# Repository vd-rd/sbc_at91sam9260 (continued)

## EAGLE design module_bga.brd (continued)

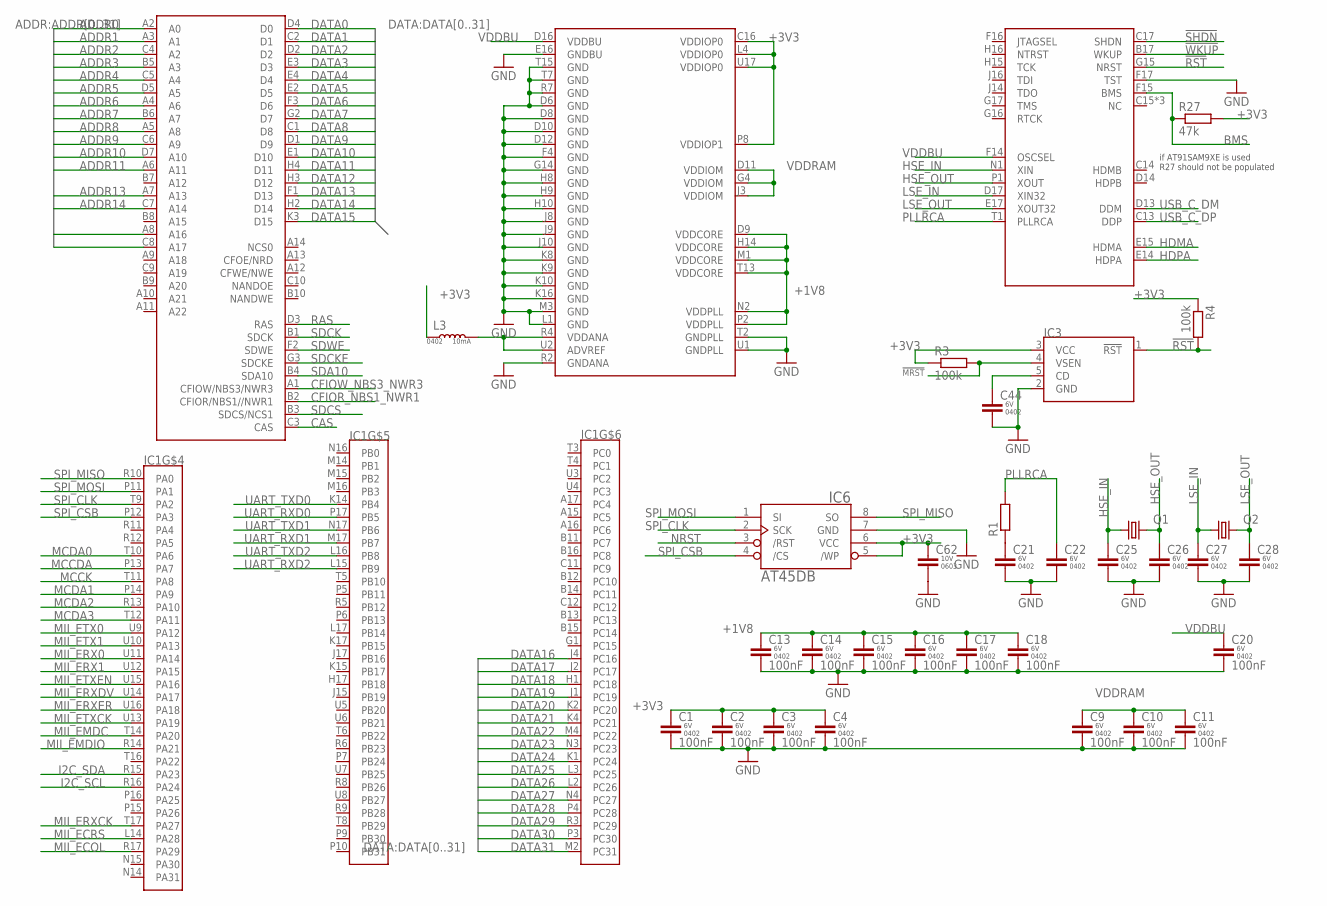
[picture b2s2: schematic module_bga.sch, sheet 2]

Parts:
C1, C2, C3, C4, C9, C10, C11, C13, C14, C15, C16, C17, C18, C20: 100nF; C0402K
C21, C22, C25, C26, C27, C28, C44: CAP-0402; C0402K
C62: CAP-0603; C0603
IC1: AT91SAM9260-BGA; BGA289C80P17X17_1500X1500X100
IC3: STM1831; SOT95P280X100-5
IC6: AT45DB-S; SOIC8_208MIL
L3: IND-0402; L0402
Q1: 3215-7; 3215
Q2: CFPX–217-NHT; 3215
R1: R-EU_R0402; R0402
R3, R4: 100k; R0402
R27: 47k; R0402

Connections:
!MRST: IC3.4 (VSEN), R3.2; also elsewhere on the board
!RST: IC1.G15 (NRST), IC3.1 (!RST), R4.2
!SHDN: IC1.C17 (SHDN)
!WKUP: IC1.B17 (WKUP); also elsewhere on the board
+1V8: C13.1, C14.1, C15.1, C16.1, C17.1, C18.1, IC1.D9 (VDDCORE), IC1.H14 (VDDCORE), IC1.M1 (VDDCORE), IC1.N2 (VDDPLL), IC1.P2 (VDDPLL), IC1.T13 (VDDCORE); also elsewhere on the board
+3V3: C1.1, C2.1, C3.1, C4.1, C62.1, IC1.C16 (VDDIOP0), IC1.L4 (VDDIOP0), IC1.P8 (VDDIOP1), IC1.U17 (VDDIOP0), IC3.3 (VCC), IC6.5 (/WP), IC6.6 (VCC), L3.1, R3.1, R4.1, R27.2; also elsewhere on the board
ADDR0: IC1.A2 (A0); also elsewhere on the board
ADDR1: IC1.A3 (A1); also elsewhere on the board
ADDR2: IC1.C4 (A2); also elsewhere on the board
ADDR3: IC1.B5 (A3); also elsewhere on the board
ADDR4: IC1.C5 (A4); also elsewhere on the board
ADDR5: IC1.D5 (A5); also elsewhere on the board
ADDR6: IC1.A4 (A6); also elsewhere on the board
ADDR7: IC1.B6 (A7); also elsewhere on the board
ADDR8: IC1.A5 (A8); also elsewhere on the board
ADDR9: IC1.C6 (A9); also elsewhere on the board
ADDR10: IC1.D7 (A10); also elsewhere on the board
ADDR11: IC1.A6 (A11); also elsewhere on the board
ADDR13: IC1.A7 (A13); also elsewhere on the board
ADDR14: IC1.C7 (A14); also elsewhere on the board
ADDR16: IC1.A8 (A16); also elsewhere on the board
ADDR17: IC1.C8 (A17); also elsewhere on the board
BMS: IC1.F15 (BMS), R27.1
CAS: IC1.C3 (CAS); also elsewhere on the board
CFIOR_NBS1_NWR1: IC1.B2 (CFIOR/NBS1//NWR1); also elsewhere on the board
CFIOW_NBS3_NWR3: IC1.A1 (CFIOW/NBS3/NWR3); also elsewhere on the board
DATA0: IC1.D4 (D0); also elsewhere on the board
DATA1: IC1.C2 (D1); also elsewhere on the board
DATA2: IC1.D2; also elsewhere on the board
DATA3: IC1.E3 (D3); also elsewhere on the board
DATA4: IC1.E4 (D4); also elsewhere on the board
DATA5: IC1.E2 (D5); also elsewhere on the board
DATA6: IC1.F3 (D6); also elsewhere on the board
DATA7: IC1.G2 (D7); also elsewhere on the board
DATA8: IC1.C1 (D8); also elsewhere on the board
DATA9: IC1.D1 (D9); also elsewhere on the board
DATA10: IC1.E1 (D10); also elsewhere on the board
DATA11: IC1.H4 (D11); also elsewhere on the board
DATA12: IC1.H3 (D12); also elsewhere on the board
DATA13: IC1.F1 (D13); also elsewhere on the board
DATA14: IC1.H2 (D14); also elsewhere on the board
DATA15: IC1.K3 (D15); also elsewhere on the board
DATA16: IC1.J4 (PC16); also elsewhere on the board
DATA17: IC1.J2 (PC17); also elsewhere on the board
DATA18: IC1.H1 (PC18); also elsewhere on the board
DATA19: IC1.J1 (PC19); also elsewhere on the board
DATA20: IC1.K2 (PC20); also elsewhere on the board
DATA21: IC1.K4 (PC21); also elsewhere on the board
DATA22: IC1.M4 (PC22); also elsewhere on the board
DATA23: IC1.N3 (PC23); also elsewhere on the board
DATA24: IC1.K1 (PC24); also elsewhere on the board
DATA25: IC1.L3 (PC25); also elsewhere on the board
DATA26: IC1.L2 (PC26); also elsewhere on the board
DATA27: IC1.N4 (PC27); also elsewhere on the board
DATA28: IC1.P4 (PC28); also elsewhere on the board
DATA29: IC1.R3 (PC29); also elsewhere on the board
DATA30: IC1.P3 (PC30); also elsewhere on the board
DATA31: IC1.M2 (PC31); also elsewhere on the board
GND: C1.2, C2.2, C3.2, C4.2, C9.2, C10.2, C11.2, C13.2, C14.2, C15.2, C16.2, C17.2, C18.2, C20.2, C21.2, C22.2, C25.2, C26.2, C27.2, C28.2, C44.2, C62.2, IC1.D6 (GND), IC1.D8 (GND), IC1.D10 (GND), IC1.D12 (GND), IC1.E16 (GNDBU), IC1.F4 (GND), IC1.F17 (TST), IC1.G14 (GND), IC1.H8 (GND), IC1.H9 (GND), IC1.H10 (GND), IC1.J8 (GND), IC1.J9 (GND), IC1.J10 (GND), IC1.K8 (GND), IC1.K9 (GND), IC1.K10 (GND), IC1.K16 (GND), IC1.L1 (GND), IC1.M3 (GND), IC1.R2 (GNDANA), IC1.R7 (GND), IC1.T2 (GNDPLL), IC1.T7 (GND), IC1.T15 (GND), IC1.U1 (GNDPLL), IC3.2 (GND), IC6.7 (GND); also elsewhere on the board
HDMA: IC1.E15 (HDMA); also elsewhere on the board
HDPA: IC1.E14 (HDPA); also elsewhere on the board
HSE_IN: C25.1, IC1.N1 (XIN), Q1.1
HSE_OUT: C26.1, IC1.P1 (XOUT), Q1.3 (2)
I2C_SCL: IC1.R16 (PA24); also elsewhere on the board
I2C_SDA: IC1.R15 (PA23); also elsewhere on the board
LSE_IN: C27.1, IC1.D17 (XIN32), Q2.1
LSE_OUT: C28.1, IC1.E17 (XOUT32), Q2.2
MCCDA: IC1.P13 (PA7); also elsewhere on the board
MCCK: IC1.T11 (PA8); also elsewhere on the board
MCDA0: IC1.T10 (PA6); also elsewhere on the board
MCDA1: IC1.P14 (PA9); also elsewhere on the board
MCDA2: IC1.R13 (PA10); also elsewhere on the board
MCDA3: IC1.T12 (PA11); also elsewhere on the board
MII_ECOL: IC1.R17 (PA29)
MII_ECRS: IC1.L14 (PA28)
MII_EMDC: IC1.T14 (PA20)
MII_EMDIO: IC1.R14 (PA21)
MII_ERX0: IC1.U11 (PA14)
MII_ERX1: IC1.U12 (PA15)
MII_ERXCK: IC1.T17 (PA27)
MII_ERXDV: IC1.U14 (PA17)
MII_ERXER: IC1.U16 (PA18)
MII_ETX0: IC1.U9 (PA12)
MII_ETX1: IC1.U10 (PA13)
MII_ETXCK: IC1.U13 (PA19)
MII_ETXEN: IC1.U15 (PA16)
unnamed: C21.1, R1.1
unnamed: C44.1, IC3.5 (CD)
unnamed: IC1.R4 (VDDANA), IC1.U2 (ADVREF), L3.2
NRST: IC6.3 (/RST); also elsewhere on the board
PLLRCA: C22.1, IC1.T1 (PLLRCA), R1.2
RAS: IC1.D3 (RAS); also elsewhere on the board
SDA10: IC1.B4 (SDA10); also elsewhere on the board
SDCK: IC1.B1 (SDCK); also elsewhere on the board
SDCKE: IC1.G3 (SDCKE); also elsewhere on the board
SDCS: IC1.B3 (SDCS/NCS1); also elsewhere on the board
SDWE: IC1.F2 (SDWE); also elsewhere on the board
SPI_CLK: IC1.T9 (PA2), IC6.2 (SCK); also elsewhere on the board
SPI_CSB: IC1.P12 (PA3), IC6.4 (/CS)
SPI_MISO: IC1.R10 (PA0), IC6.8 (SO); also elsewhere on the board
SPI_MOSI: IC1.P11 (PA1), IC6.1 (SI); also elsewhere on the board
UART_RXD0: IC1.P17 (PB5); also elsewhere on the board
UART_RXD1: IC1.M17 (PB7); also elsewhere on the board
UART_RXD2: IC1.L15 (PB9); also elsewhere on the board
UART_TXD0: IC1.K14 (PB4); also elsewhere on the board
UART_TXD1: IC1.N17 (PB6); also elsewhere on the board
UART_TXD2: IC1.L16 (PB8); also elsewhere on the board
USB_C_DM: IC1.D13 (DDM); also elsewhere on the board
USB_C_DP: IC1.C13 (DDP); also elsewhere on the board
VDDBU: C20.1, IC1.D16 (VDDBU), IC1.F14 (OSCSEL)
VDDRAM: C9.1, C10.1, C11.1, IC1.D11 (VDDIOM), IC1.G4 (VDDIOM), IC1.J3 (VDDIOM); also elsewhere on the board

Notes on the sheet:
if AT91SAM9XE is used R27 should not be populated

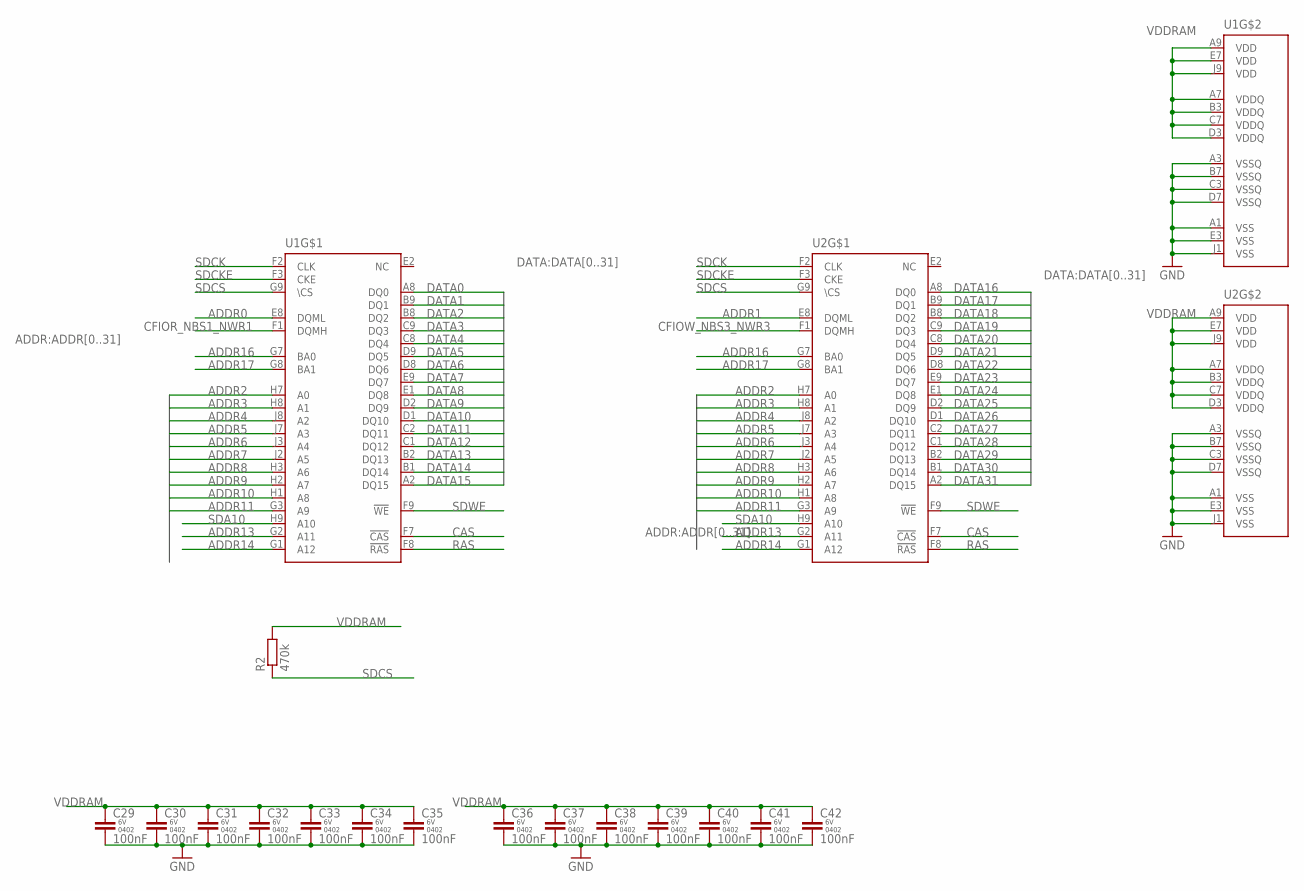
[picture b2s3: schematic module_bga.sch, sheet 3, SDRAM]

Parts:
C29, C30, C31, C32, C33, C34, C35, C36, C37, C38, C39, C40, C41, C42: 100nF; C0402K
R2: 470k; R0402
U1, U2: IS42S16160G; BGA81C80P9X9_800X800X120

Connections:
ADDR0: U1.E8 (DQML); also elsewhere on the board
ADDR1: U2.E8 (DQML); also elsewhere on the board
ADDR2: U1.H7 (A0), U2.H7 (A0); also elsewhere on the board
ADDR3: U1.H8 (A1), U2.H8 (A1); also elsewhere on the board
ADDR4: U1.J8 (A2), U2.J8 (A2); also elsewhere on the board
ADDR5: U1.J7 (A3), U2.J7 (A3); also elsewhere on the board
ADDR6: U1.J3 (A4), U2.J3 (A4); also elsewhere on the board
ADDR7: U1.J2 (A5), U2.J2 (A5); also elsewhere on the board
ADDR8: U1.H3 (A6), U2.H3 (A6); also elsewhere on the board
ADDR9: U1.H2 (A7), U2.H2 (A7); also elsewhere on the board
ADDR10: U1.H1 (A8), U2.H1 (A8); also elsewhere on the board
ADDR11: U1.G3 (A9), U2.G3 (A9); also elsewhere on the board
ADDR13: U1.G2 (A11), U2.G2 (A11); also elsewhere on the board
ADDR14: U1.G1 (A12), U2.G1 (A12); also elsewhere on the board
ADDR16: U1.G7 (BA0), U2.G7 (BA0); also elsewhere on the board
ADDR17: U1.G8 (BA1), U2.G8 (BA1); also elsewhere on the board
CAS: U1.F7 (!CAS), U2.F7 (!CAS); also elsewhere on the board
CFIOR_NBS1_NWR1: U1.F1 (DQMH); also elsewhere on the board
CFIOW_NBS3_NWR3: U2.F1 (DQMH); also elsewhere on the board
DATA0: U1.A8 (DQ0); also elsewhere on the board
DATA1: U1.B9 (DQ1); also elsewhere on the board
DATA2: U1.B8 (DQ2); also elsewhere on the board
DATA3: U1.C9 (DQ3); also elsewhere on the board
DATA4: U1.C8 (DQ4); also elsewhere on the board
DATA5: U1.D9 (DQ5); also elsewhere on the board
DATA6: U1.D8 (DQ6); also elsewhere on the board
DATA7: U1.E9 (DQ7); also elsewhere on the board
DATA8: U1.E1 (DQ8); also elsewhere on the board
DATA9: U1.D2 (DQ9); also elsewhere on the board
DATA10: U1.D1 (DQ10); also elsewhere on the board
DATA11: U1.C2 (DQ11); also elsewhere on the board
DATA12: U1.C1 (DQ12); also elsewhere on the board
DATA13: U1.B2 (DQ13); also elsewhere on the board
DATA14: U1.B1 (DQ14); also elsewhere on the board
DATA15: U1.A2 (DQ15); also elsewhere on the board
DATA16: U2.A8 (DQ0); also elsewhere on the board
DATA17: U2.B9 (DQ1); also elsewhere on the board
DATA18: U2.B8 (DQ2); also elsewhere on the board
DATA19: U2.C9 (DQ3); also elsewhere on the board
DATA20: U2.C8 (DQ4); also elsewhere on the board
DATA21: U2.D9 (DQ5); also elsewhere on the board
DATA22: U2.D8 (DQ6); also elsewhere on the board
DATA23: U2.E9 (DQ7); also elsewhere on the board
DATA24: U2.E1 (DQ8); also elsewhere on the board
DATA25: U2.D2 (DQ9); also elsewhere on the board
DATA26: U2.D1 (DQ10); also elsewhere on the board
DATA27: U2.C2 (DQ11); also elsewhere on the board
DATA28: U2.C1 (DQ12); also elsewhere on the board
DATA29: U2.B2 (DQ13); also elsewhere on the board
DATA30: U2.B1 (DQ14); also elsewhere on the board
DATA31: U2.A2 (DQ15); also elsewhere on the board
GND: C29.2, C30.2, C31.2, C32.2, C33.2, C34.2, C35.2, C36.2, C37.2, C38.2, C39.2, C40.2, C41.2, C42.2, U1.A1 (VSS), U1.A3 (VSSQ), U1.B7 (VSSQ), U1.C3 (VSSQ), U1.D7 (VSSQ), U1.E3 (VSS), U1.J1 (VSS), U2.A1 (VSS), U2.A3 (VSSQ), U2.B7 (VSSQ), U2.C3 (VSSQ), U2.D7 (VSSQ), U2.E3 (VSS), U2.J1 (VSS); also elsewhere on the board
RAS: U1.F8 (!RAS), U2.F8 (!RAS); also elsewhere on the board
SDA10: U1.H9 (A10), U2.H9 (A10); also elsewhere on the board
SDCK: U1.F2 (CLK), U2.F2 (CLK); also elsewhere on the board
SDCKE: U1.F3 (CKE), U2.F3 (CKE); also elsewhere on the board
SDCS: R2.1, U1.G9 (\CS), U2.G9 (\CS); also elsewhere on the board
SDWE: U1.F9 (!WE), U2.F9 (!WE); also elsewhere on the board
VDDRAM: C29.1, C30.1, C31.1, C32.1, C33.1, C34.1, C35.1, C36.1, C37.1, C38.1, C39.1, C40.1, C41.1, C42.1, R2.2, U1.A7 (VDDQ), U1.A9 (VDD), U1.B3 (VDDQ), U1.C7 (VDDQ), U1.D3 (VDDQ), U1.E7 (VDD), U1.J9 (VDD), U2.A7 (VDDQ), U2.A9 (VDD), U2.B3 (VDDQ), U2.C7 (VDDQ), U2.D3 (VDDQ), U2.E7 (VDD), U2.J9 (VDD); also elsewhere on the board

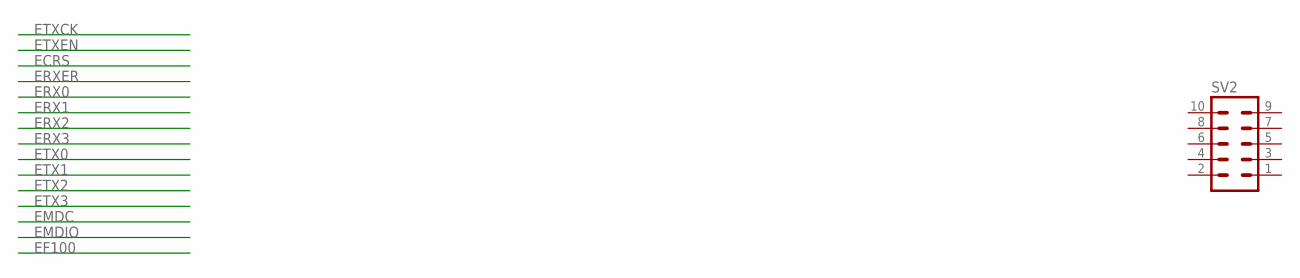
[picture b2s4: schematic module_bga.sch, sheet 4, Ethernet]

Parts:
SV2: MA05-2

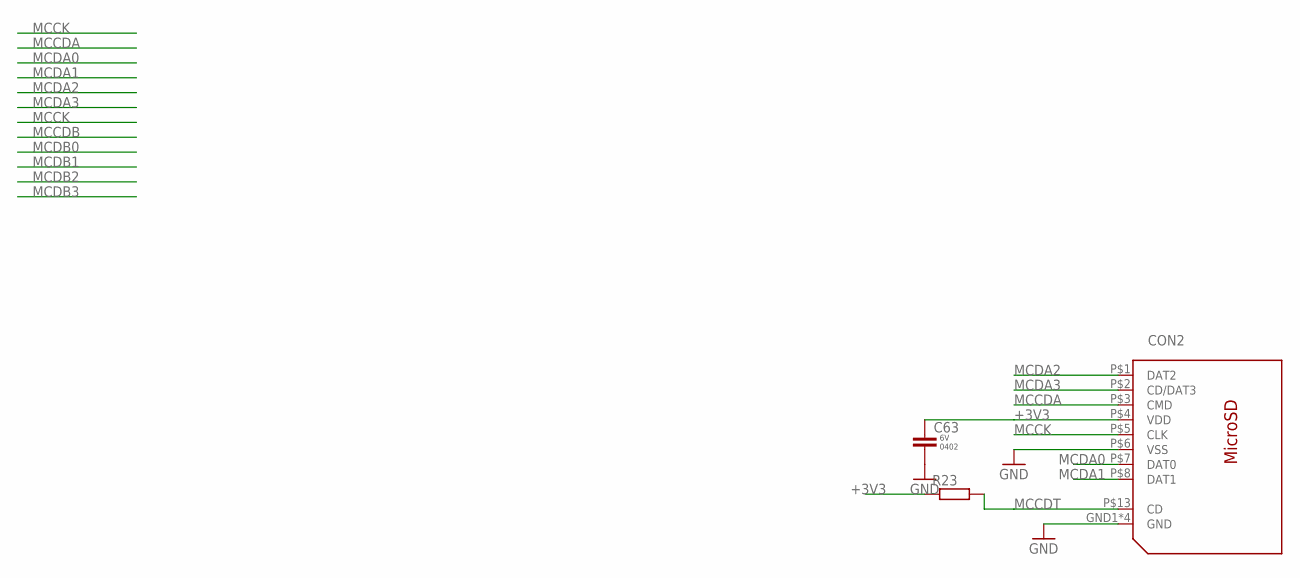
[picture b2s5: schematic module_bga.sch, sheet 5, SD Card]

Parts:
C63: CAP-0402; C0402K
CON2: 112J-TXAR; 112J
R23: R-EU_R0402; R0402

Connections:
+3V3: C63.1, CON2.P$4 (VDD), R23.1; also elsewhere on the board
GND: C63.2, CON2.GND1 (GND), CON2.GND2 (GND), CON2.GND3 (GND), CON2.GND4 (GND), CON2.P$6 (VSS); also elsewhere on the board
MCCDA: CON2.P$3 (CMD); also elsewhere on the board
MCCDT: CON2.P$13 (CD), R23.2
MCCK: CON2.P$5 (CLK); also elsewhere on the board
MCDA0: CON2.P$7 (DAT0); also elsewhere on the board
MCDA1: CON2.P$8 (DAT1); also elsewhere on the board
MCDA2: CON2.P$1 (DAT2); also elsewhere on the board
MCDA3: CON2.P$2 (CD/DAT3); also elsewhere on the board

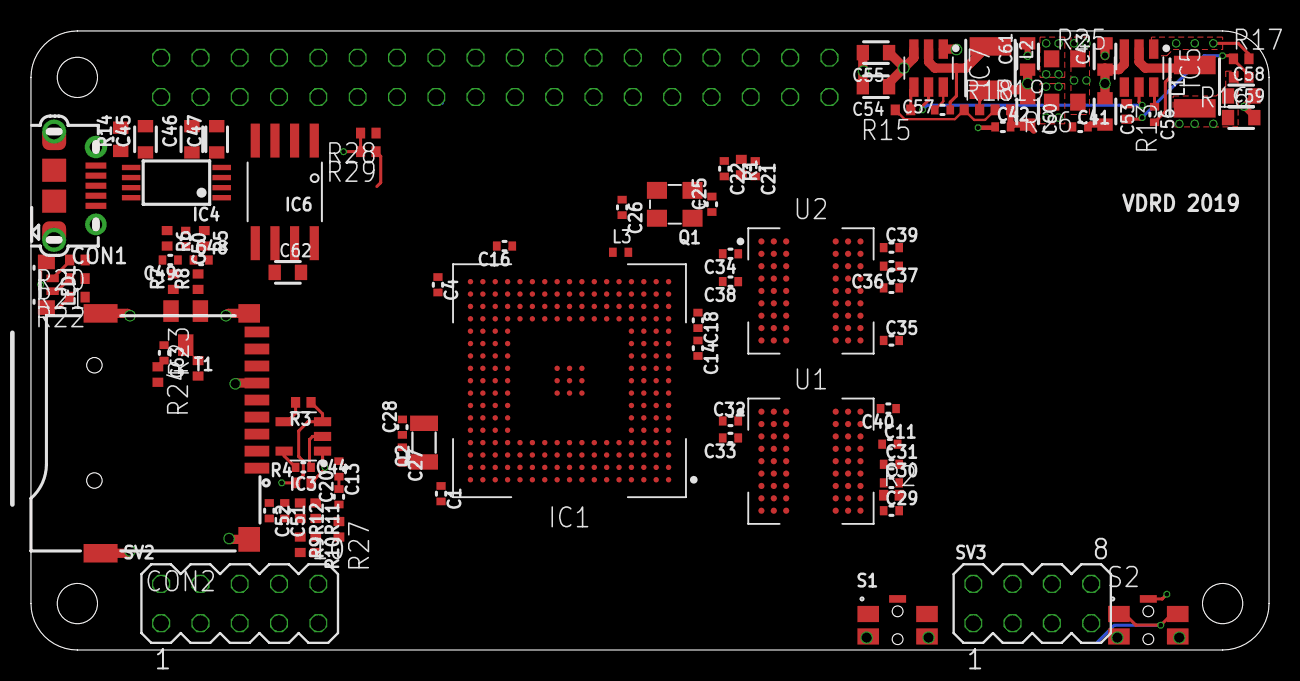
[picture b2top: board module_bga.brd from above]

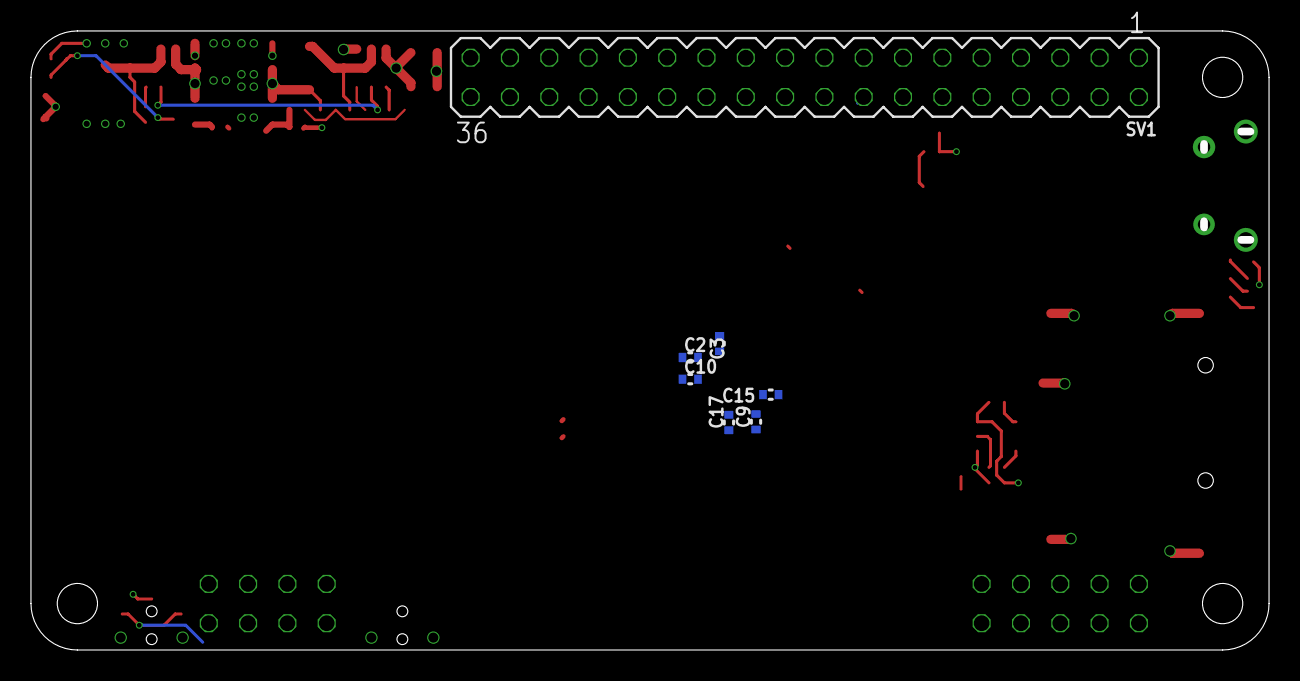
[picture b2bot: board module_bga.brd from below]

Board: 4 copper layers, 80.0 x 40.0 mm, 106 parts (7 on the bottom side), 121 nets.

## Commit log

2019-04-16 repo bringup
2019-04-16 defined connections
2019-04-17 cleaned up schematic
2019-04-17 finished power distribution
2019-04-17 layout: sdram traces
2019-04-17 schematic: add shdn button
2019-04-17 layout: sdram addr traces
2019-04-17 board: add switch for ram voltage
2019-04-17 board: more routed signals
2019-04-18 layout: length matching
2019-04-18 updated description
2019-04-18 Backlink to CADLAB.io has been added.
2019-04-19 board: make board compatible with at91sam9xe
2019-04-19 board: arranged parts
2019-04-19 board: add pm buttons
2019-04-19 board: fix dataflash connections
2019-04-19 added bga variant
2019-04-22 board: adjusted usb host connector
2019-04-22 layout: fixed power distribution traces
2019-04-22 layout: fixes to ensure spacing for board mechanical mounts
2019-04-22 board: removed buttons
2019-04-22 layout: arranged usb host components
2019-04-22 layout: moved LSE to make room for RMII signals'
2019-04-22 schematic: rmii connector 1st draft
2019-04-22 schematic: defined gpio connections
2019-04-22 layout: routed gpio
2019-04-25 schematic: added missing passives for proper boot-up
2019-04-25 layout: optimised component descriptor placement
2019-04-25 board: update render
2019-04-25 layout: small fixes
2019-04-26 board: added fiducials
2019-05-03 schematic: added values for step-down
2019-05-07 layout: minor improvements
2019-05-07 board: add missing usb detection circuitry
2019-05-08 project: updated documentation
2019-05-10 project: updated structure
2019-05-10 layout: rmii bus routing
2019-05-11 board: minor fixes
2019-05-11 layout: finished rmii connections
2019-05-11 bpard: remove unused features
2019-05-12 board: modified minimum via size
2019-05-12 board: passed drc
2019-05-12 board: cosmetic fixes
2019-05-14 Create BOOT.,md
2019-05-15 board: add signal legend
2019-05-16 project: board ready for fab
2019-05-20 board: fixed wrong pinout
2019-05-21 project: fixed typo
2019-06-04 project: added assets
2019-06-04 project: added boot flow diagram
2021-02-18 Update changelog
2021-02-20 Fixed typo
2021-02-22 project: add recovery test-point
2021-03-03 fix wrong footprint for microsd card
2021-03-03 tweak feedback network values
2021-03-04 Set theme jekyll-theme-hacker
2021-03-04 Create CNAME
2022-04-08 preprare new revision for fab
2022-04-12 prepare for new board version to send in fab
2022-05-22 improve eth header for compatibility
